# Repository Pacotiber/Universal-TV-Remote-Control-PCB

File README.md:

# 💣 Universal IR TV Remote — "Timer Bomb" Edition

A universal infrared remote control built around a **XIAO ESP32**, designed to automatically turn off a TV after a set countdown — or instantly, on demand.

## 📋 Overview

- ⏱️ A **30-minute timer** counts down and shows the remaining time on an OLED screen.
- 📡 When the timer hits zero, the XIAO ESP32 automatically sends an **IR POWER command** to switch off the TV.
- 🔴 A second push button lets you **turn off the TV instantly**, without waiting for the timer.
- 👁️ A **photoresistor (LDR)** checks the ambient light after the command is sent to confirm whether the TV actually turned off.
- 🟢 **Green LED** → TV detected as off.
- 🔴 **Red LED** → TV still seems to be on.
- The IR LED is driven through a **transistor** for a stronger, more reliable signal.

The PCB itself is designed and shaped like a **stick of dynamite** — a small joke: the countdown reaches zero, but instead of an explosion, the TV just switches off. 😄

## ⚙️ How It Works

1. Power on the device — the timer starts automatically at 30:00.
2. The remaining time is displayed live on the OLED screen.
3. At any point, press the **instant-off button** to send the IR power command right away.
4. Otherwise, once the timer reaches 0, the IR command is sent automatically.
5. The LDR reads the ambient brightness and lights up the green or red LED depending on whether the TV appears off.

## 🔧 Main Components

| Component | Role |
|---|---|
| **Seeed XIAO ESP32** | Main microcontroller |
| **OLED display (I2C, 0.91")** | Shows the countdown timer |
| **IR LED + transistor (BC108)** | Sends the IR POWER command |
| **Photoresistor (LDR)** | Detects TV screen brightness |
| **RGB LED** | Status indicator (TV off / TV on) |
| **2x push buttons** | Instant shutdown / control |
| **Custom PCB (KiCad)** | Bomb-shaped board hosting all components |

## 📷 Photos

**Real circuit:**

**PCB (KiCad layout):**

**3D view:**

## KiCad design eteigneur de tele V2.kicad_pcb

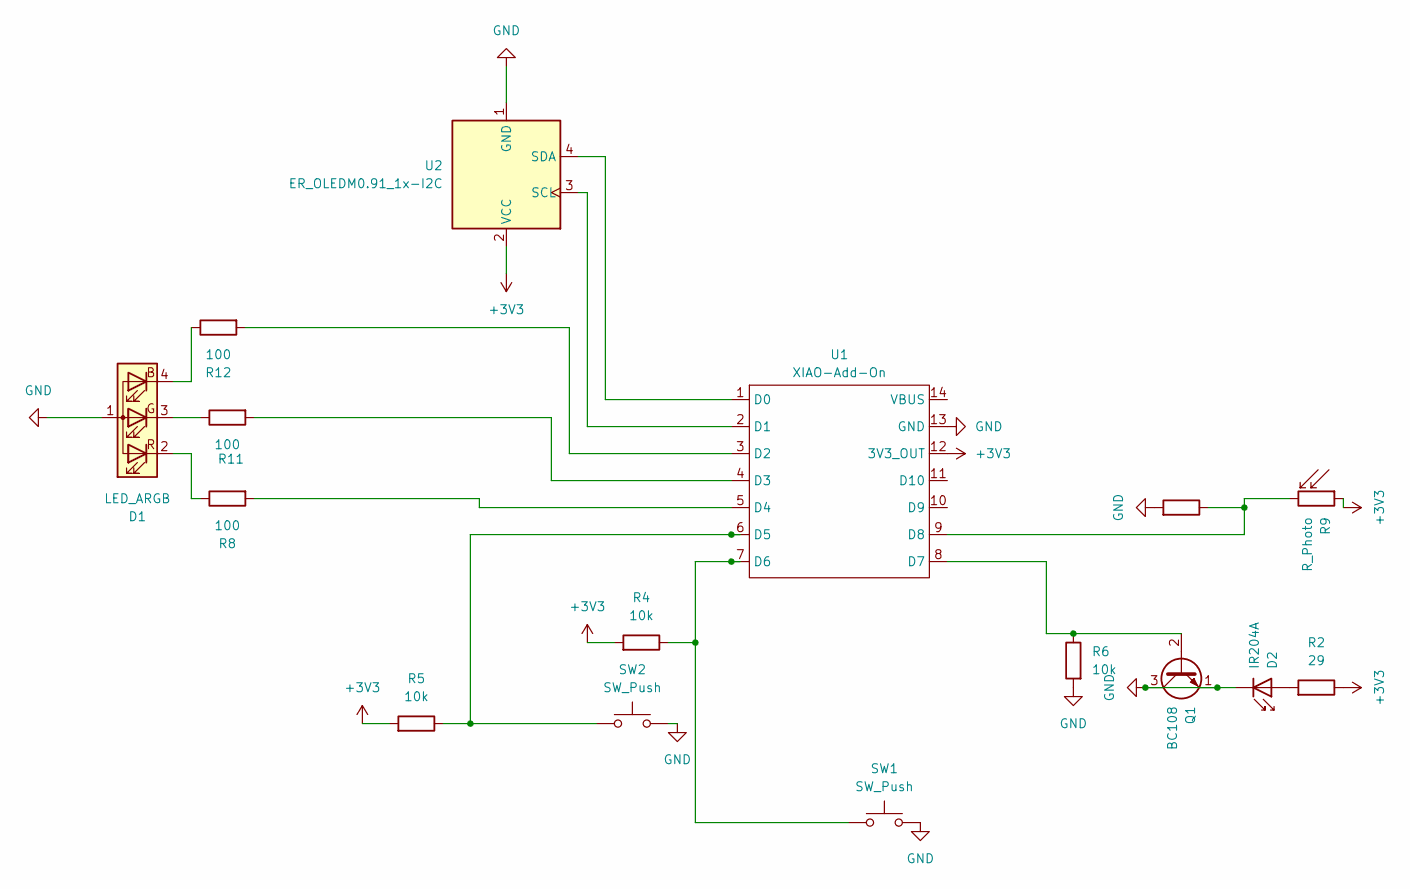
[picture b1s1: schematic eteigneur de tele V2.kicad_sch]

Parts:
D1: LED_ARGB; LED_D5.0mm-4_RGB_Wide_Pins
D2: IR204A; LED_D3.0mm_IRBlack
Q1: BC108; SOT-23-3
R2: 29; R_0805_2012Metric
R4, R5, R6, R10: 10k; R_0805_2012Metric
R8, R11, R12: 100; R_0805_2012Metric
R9: R_Photo; R_LDR_10x8.5mm_P7.6mm_Vertical
SW1, SW2: SW_Push; PTS526SK15SMTR2LFS
U1: XIAO-Add-On; XIAO-ESP32S3-DIP
U2: ER_OLEDM0.91_1x-I2C; SSD1306_module

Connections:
+3V3: R2.1, R4.2, R5.2, R9.1, U1.12 (3V3_OUT), U2.2 (VCC)
GND: D1.1 (A), D2.1 (K), Q1.1 (E), Q1.3 (C), R6.2, R10.2, SW1.2, SW2.2, U1.13 (GND), U2.1 (GND)
unnamed: D1.4 (BK), R12.1
unnamed: D1.3 (GK), R11.1
unnamed: D1.2 (RK), R8.1
unnamed: D2.2 (A), R2.2
unnamed: Q1.2 (B), R6.1, U1.8 (D7)
unnamed: U1.1 (D0), U2.4 (SDA)
unnamed: U1.2 (D1), U2.3 (SCL)
unnamed: R12.2, U1.3 (D2)
unnamed: R11.2, U1.4 (D3)
unnamed: R8.2, U1.5 (D4)
unnamed: R5.1, SW2.1, U1.6 (D5)
unnamed: R4.1, SW1.1, U1.7 (D6)
unnamed: R9.2, R10.1, U1.9 (D8)

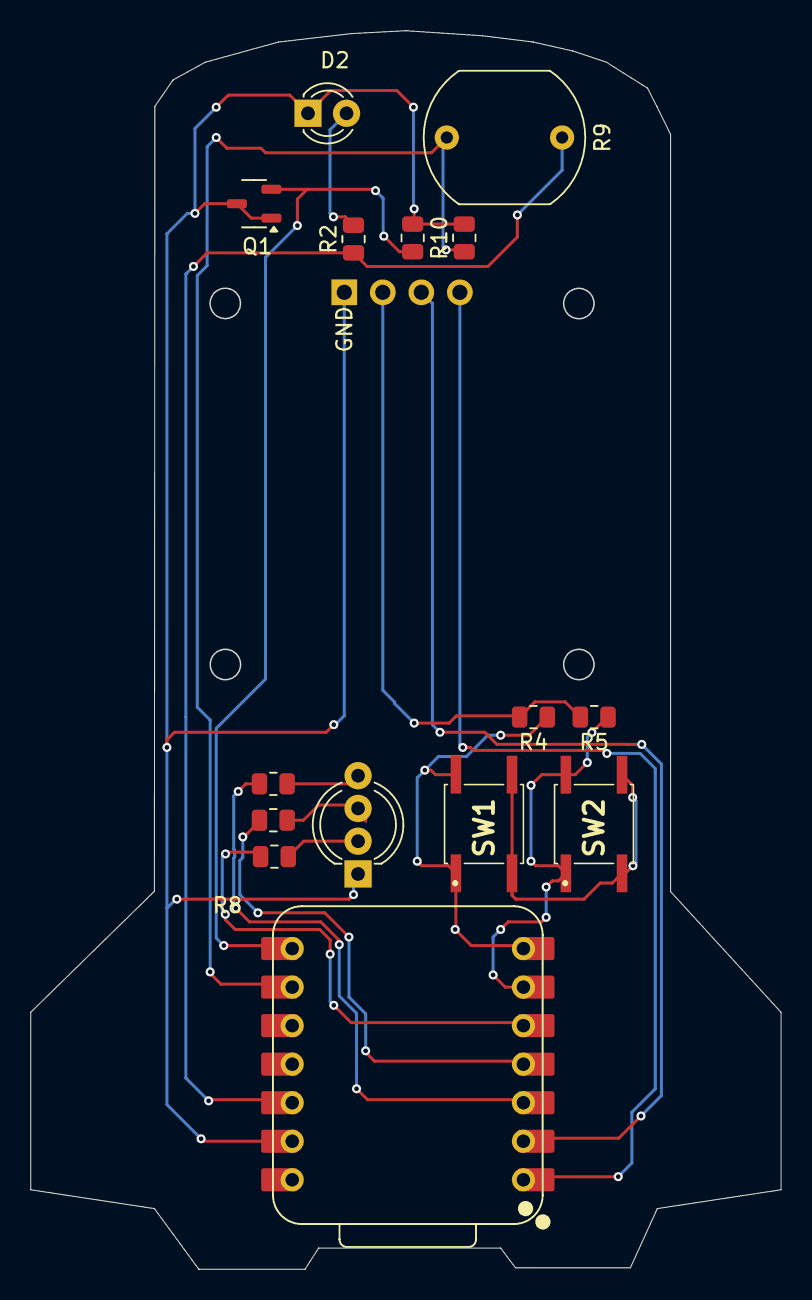
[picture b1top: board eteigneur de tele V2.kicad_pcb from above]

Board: 2 copper layers, 49.5 x 81.6 mm, 16 parts (0 on the bottom side), 15 nets.
